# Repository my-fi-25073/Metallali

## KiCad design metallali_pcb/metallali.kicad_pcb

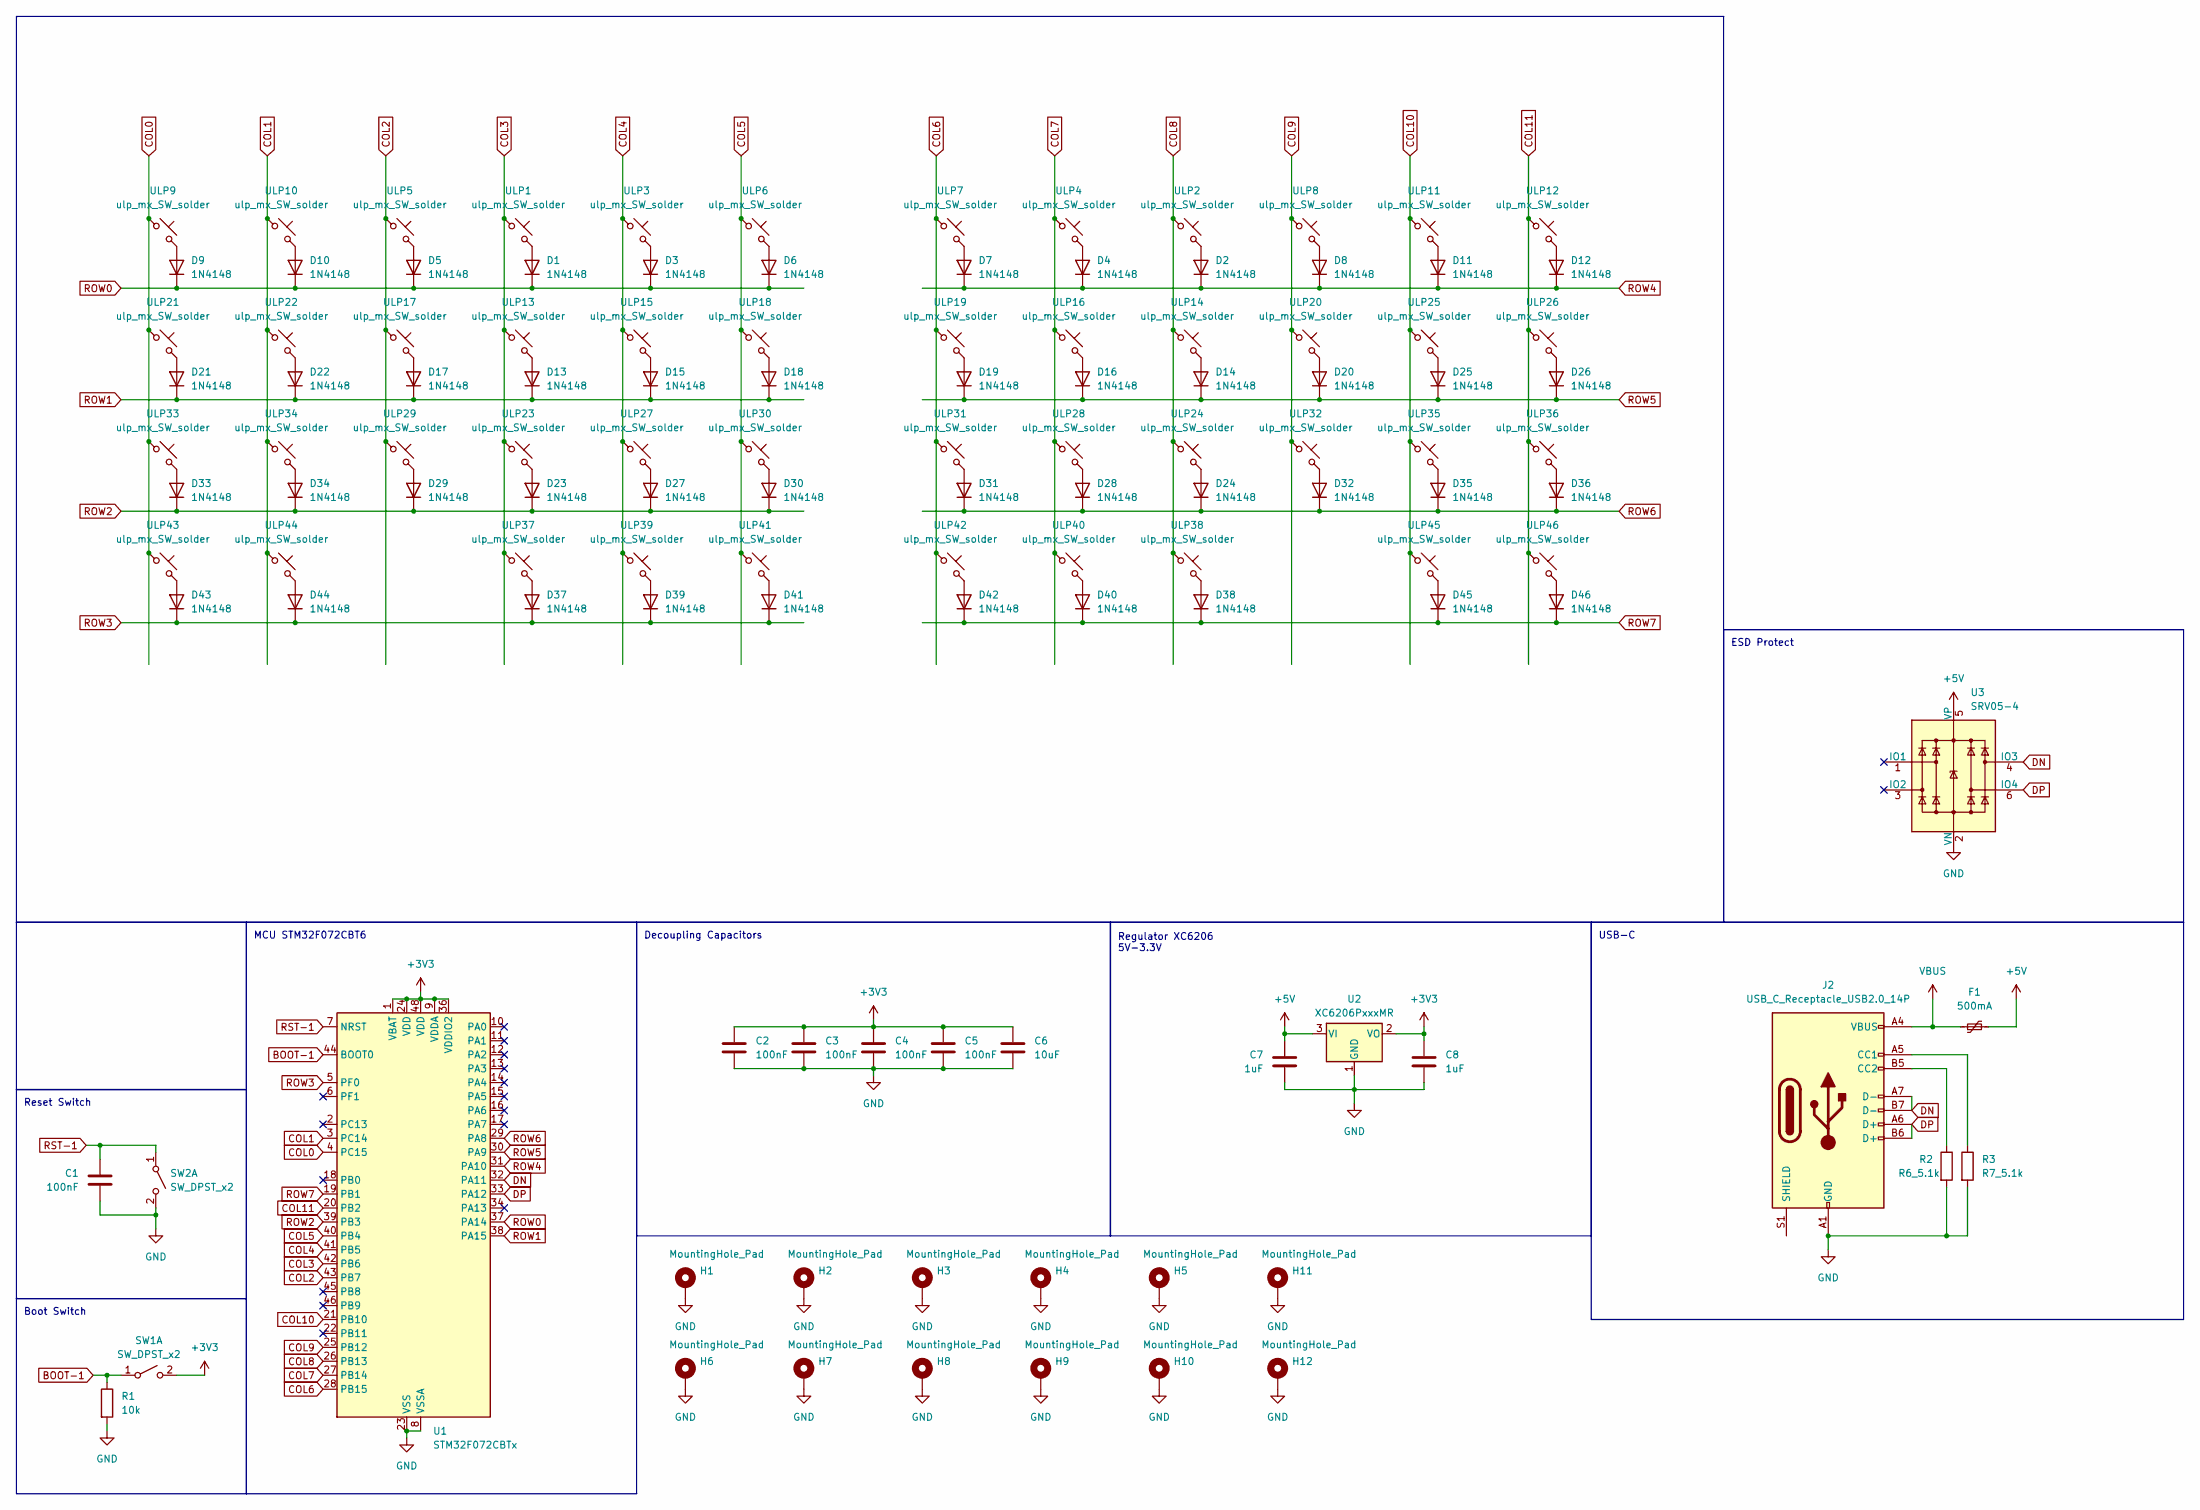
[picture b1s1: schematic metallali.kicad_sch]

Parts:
C1, C2, C3, C4, C5: 100nF; C_0402_1005Metric
C6: 10uF; C_0402_1005Metric
C7, C8: 1uF; C_0402_1005Metric
D1, D2, D3, D4, D5, D6, D7, D8, D9, D10, D11, D12, D13, D14, D15, D16, D17, D18, D19, D20, D21, D22, D23, D24, D25, D26, D27, D28, D29, D30, D31, D32, D33, D34, D35, D36, D37, D38, D39, D40, D41, D42, D43, D44, D45, D46: 1N4148; D_SOD-323
F1: 500mA; Fuse_1206_3216Metric; LCSC C70076
H1, H2, H3, H4, H5, H6, H7, H8, H9, H10, H11, H12: MountingHole_Pad; MountingHole_3.2mm_M3_ISO14580_Pad
J2: USB_C_Receptacle_USB2.0_14P; USB_C_Receptacle_HRO_TYPE-C-31-M-12; MPN C2894897
R1: 10k; R_0402_1005Metric
R2: R6_5.1k; R_0402_1005Metric
R3: R7_5.1k; R_0402_1005Metric
SW1, SW2: SW_DPST_x2; SW_Push_1P1T_XKB_TS-1187A; MPN C318884
U1: STM32F072CBTx; LQFP-48_7x7mm_P0.5mm; MPN C81720
U2: XC6206PxxxMR; SOT-23-3; MPN C5148692
U3: SRV05-4; SOT-23-6; MPN C7420376
ULP1, ULP2, ULP3, ULP4, ULP5, ULP6, ULP7, ULP8, ULP9, ULP10, ULP11, ULP12, ULP13, ULP14, ULP15, ULP16, ULP17, ULP18, ULP19, ULP20, ULP21, ULP22, ULP23, ULP24, ULP25, ULP26, ULP27, ULP28, ULP29, ULP30, ULP31, ULP32, ULP33, ULP34, ULP35, ULP36, ULP37, ULP38, ULP39, ULP40, ULP41, ULP42, ULP43, ULP44, ULP45, ULP46: ulp_mx_SW_solder; SW_MX_ULP_1u

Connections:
+3V3: C2.1, C3.1, C4.1, C5.1, C6.1, C8.1, SW1.2 (B), U1.1 (VBAT), U1.9 (VDDA), U1.24 (VDD), U1.36 (VDDIO2), U1.48 (VDD), U2.2 (VO)
+5V: C7.1, F1.2, U2.3 (VI), U3.5 (VP)
BOOT-1: R1.1, SW1.1 (A), U1.44 (BOOT0)
COL0: U1.4 (PC15), ULP9.1, ULP21.1, ULP33.1, ULP43.1
COL1: U1.3 (PC14), ULP10.1, ULP22.1, ULP34.1, ULP44.1
COL2: U1.43 (PB7), ULP5.1, ULP17.1, ULP29.1
COL3: U1.42 (PB6), ULP1.1, ULP13.1, ULP23.1, ULP37.1
COL4: U1.41 (PB5), ULP3.1, ULP15.1, ULP27.1, ULP39.1
COL5: U1.40 (PB4), ULP6.1, ULP18.1, ULP30.1, ULP41.1
COL6: U1.28 (PB15), ULP7.1, ULP19.1, ULP31.1, ULP42.1
COL7: U1.27 (PB14), ULP4.1, ULP16.1, ULP28.1, ULP40.1
COL8: U1.26 (PB13), ULP2.1, ULP14.1, ULP24.1, ULP38.1
COL9: U1.25 (PB12), ULP8.1, ULP20.1, ULP32.1
COL10: U1.21 (PB10), ULP11.1, ULP25.1, ULP35.1, ULP45.1
COL11: U1.20 (PB2), ULP12.1, ULP26.1, ULP36.1, ULP46.1
DN: J2.A7 (D-), J2.B7 (D-), U1.32 (PA11), U3.4 (IO3)
DP: J2.A6 (D+), J2.B6 (D+), U1.33 (PA12), U3.6 (IO4)
GND: C1.2, C2.2, C3.2, C4.2, C5.2, C6.2, C7.2, C8.2, H1.1, H2.1, H3.1, H4.1, H5.1, H6.1, H7.1, H8.1, H9.1, H10.1, H11.1, H12.1, J2.A1 (GND), J2.A12 (GND), J2.B1 (GND), J2.B12 (GND), R1.2, R2.2, R3.2, SW2.2 (B), U1.8 (VSSA), U1.23 (VSS), U1.35 (VSS), U1.47 (VSS), U2.1 (GND), U3.2 (VN)
unnamed: D1.2 (A), ULP1.2
unnamed: D2.2 (A), ULP2.2
unnamed: D3.2 (A), ULP3.2
unnamed: D4.2 (A), ULP4.2
unnamed: D5.2 (A), ULP5.2
unnamed: D6.2 (A), ULP6.2
unnamed: D7.2 (A), ULP7.2
unnamed: D8.2 (A), ULP8.2
unnamed: D9.2 (A), ULP9.2
unnamed: D10.2 (A), ULP10.2
unnamed: D11.2 (A), ULP11.2
unnamed: D12.2 (A), ULP12.2
unnamed: D13.2 (A), ULP13.2
unnamed: D14.2 (A), ULP14.2
unnamed: D15.2 (A), ULP15.2
unnamed: D16.2 (A), ULP16.2
unnamed: D17.2 (A), ULP17.2
unnamed: D18.2 (A), ULP18.2
unnamed: D19.2 (A), ULP19.2
unnamed: D20.2 (A), ULP20.2
unnamed: D21.2 (A), ULP21.2
unnamed: D22.2 (A), ULP22.2
unnamed: D23.2 (A), ULP23.2
unnamed: D24.2 (A), ULP24.2
unnamed: D25.2 (A), ULP25.2
unnamed: D26.2 (A), ULP26.2
unnamed: D27.2 (A), ULP27.2
unnamed: D28.2 (A), ULP28.2
unnamed: D29.2 (A), ULP29.2
unnamed: D30.2 (A), ULP30.2
unnamed: D31.2 (A), ULP31.2
unnamed: D32.2 (A), ULP32.2
unnamed: D33.2 (A), ULP33.2
unnamed: D34.2 (A), ULP34.2
unnamed: D35.2 (A), ULP35.2
unnamed: D36.2 (A), ULP36.2
unnamed: D37.2 (A), ULP37.2
unnamed: D38.2 (A), ULP38.2
unnamed: D39.2 (A), ULP39.2
unnamed: D40.2 (A), ULP40.2
unnamed: D41.2 (A), ULP41.2
unnamed: D42.2 (A), ULP42.2
unnamed: D43.2 (A), ULP43.2
unnamed: D44.2 (A), ULP44.2
unnamed: D45.2 (A), ULP45.2
unnamed: D46.2 (A), ULP46.2
unnamed: J2.A5 (CC1), R3.1
unnamed: J2.B5 (CC2), R2.1
ROW0: D1.1 (K), D3.1 (K), D5.1 (K), D6.1 (K), D9.1 (K), D10.1 (K), U1.37 (PA14)
ROW1: D13.1 (K), D15.1 (K), D17.1 (K), D18.1 (K), D21.1 (K), D22.1 (K), U1.38 (PA15)
ROW2: D23.1 (K), D27.1 (K), D29.1 (K), D30.1 (K), D33.1 (K), D34.1 (K), U1.39 (PB3)
ROW3: D37.1 (K), D39.1 (K), D41.1 (K), D43.1 (K), D44.1 (K), U1.5 (PF0)
ROW4: D2.1 (K), D4.1 (K), D7.1 (K), D8.1 (K), D11.1 (K), D12.1 (K), U1.31 (PA10)
ROW5: D14.1 (K), D16.1 (K), D19.1 (K), D20.1 (K), D25.1 (K), D26.1 (K), U1.30 (PA9)
ROW6: D24.1 (K), D28.1 (K), D31.1 (K), D32.1 (K), D35.1 (K), D36.1 (K), U1.29 (PA8)
ROW7: D38.1 (K), D40.1 (K), D42.1 (K), D45.1 (K), D46.1 (K), U1.19 (PB1)
RST-1: C1.1, SW2.1 (A), U1.7 (NRST)
VBUS: F1.1, J2.A4 (VBUS), J2.A9 (VBUS), J2.B4 (VBUS), J2.B9 (VBUS)

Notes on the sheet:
Decoupling Capacitors
MCU STM32F072CBT6
Reset Switch
USB-C
Regulator XC6206 5V-3.3V
Boot Switch
ESD Protect

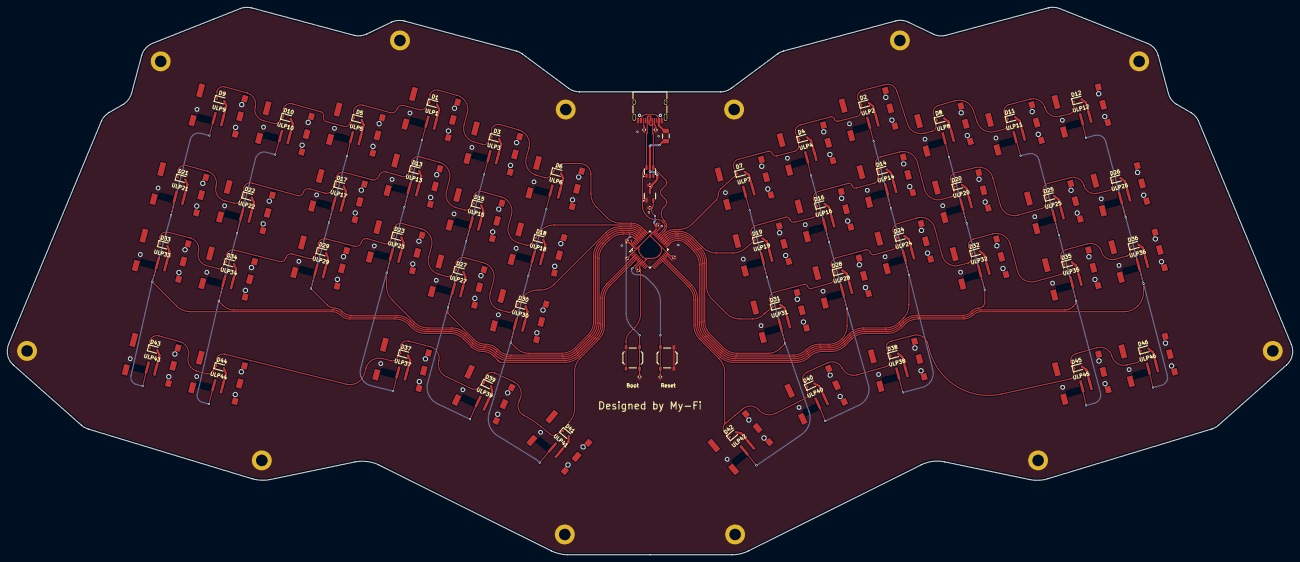
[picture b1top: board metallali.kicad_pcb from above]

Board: 2 copper layers, 355.7 x 151.5 mm, 122 parts (0 on the bottom side), 76 nets.

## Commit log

2025-04-30 Added schematics, pcb design
2025-05-01 Routed matrix
2025-05-02 Almost done! Just need to draw the outline of the PCB.
2025-05-03 Finished v1.0.00 pcb
2025-05-08 updated pcb plates
